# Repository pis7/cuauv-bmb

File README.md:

See full documentation here: https://drive.google.com/file/d/17dhruCo_O_wMr_B44XDcn42W5i2I06rd/view

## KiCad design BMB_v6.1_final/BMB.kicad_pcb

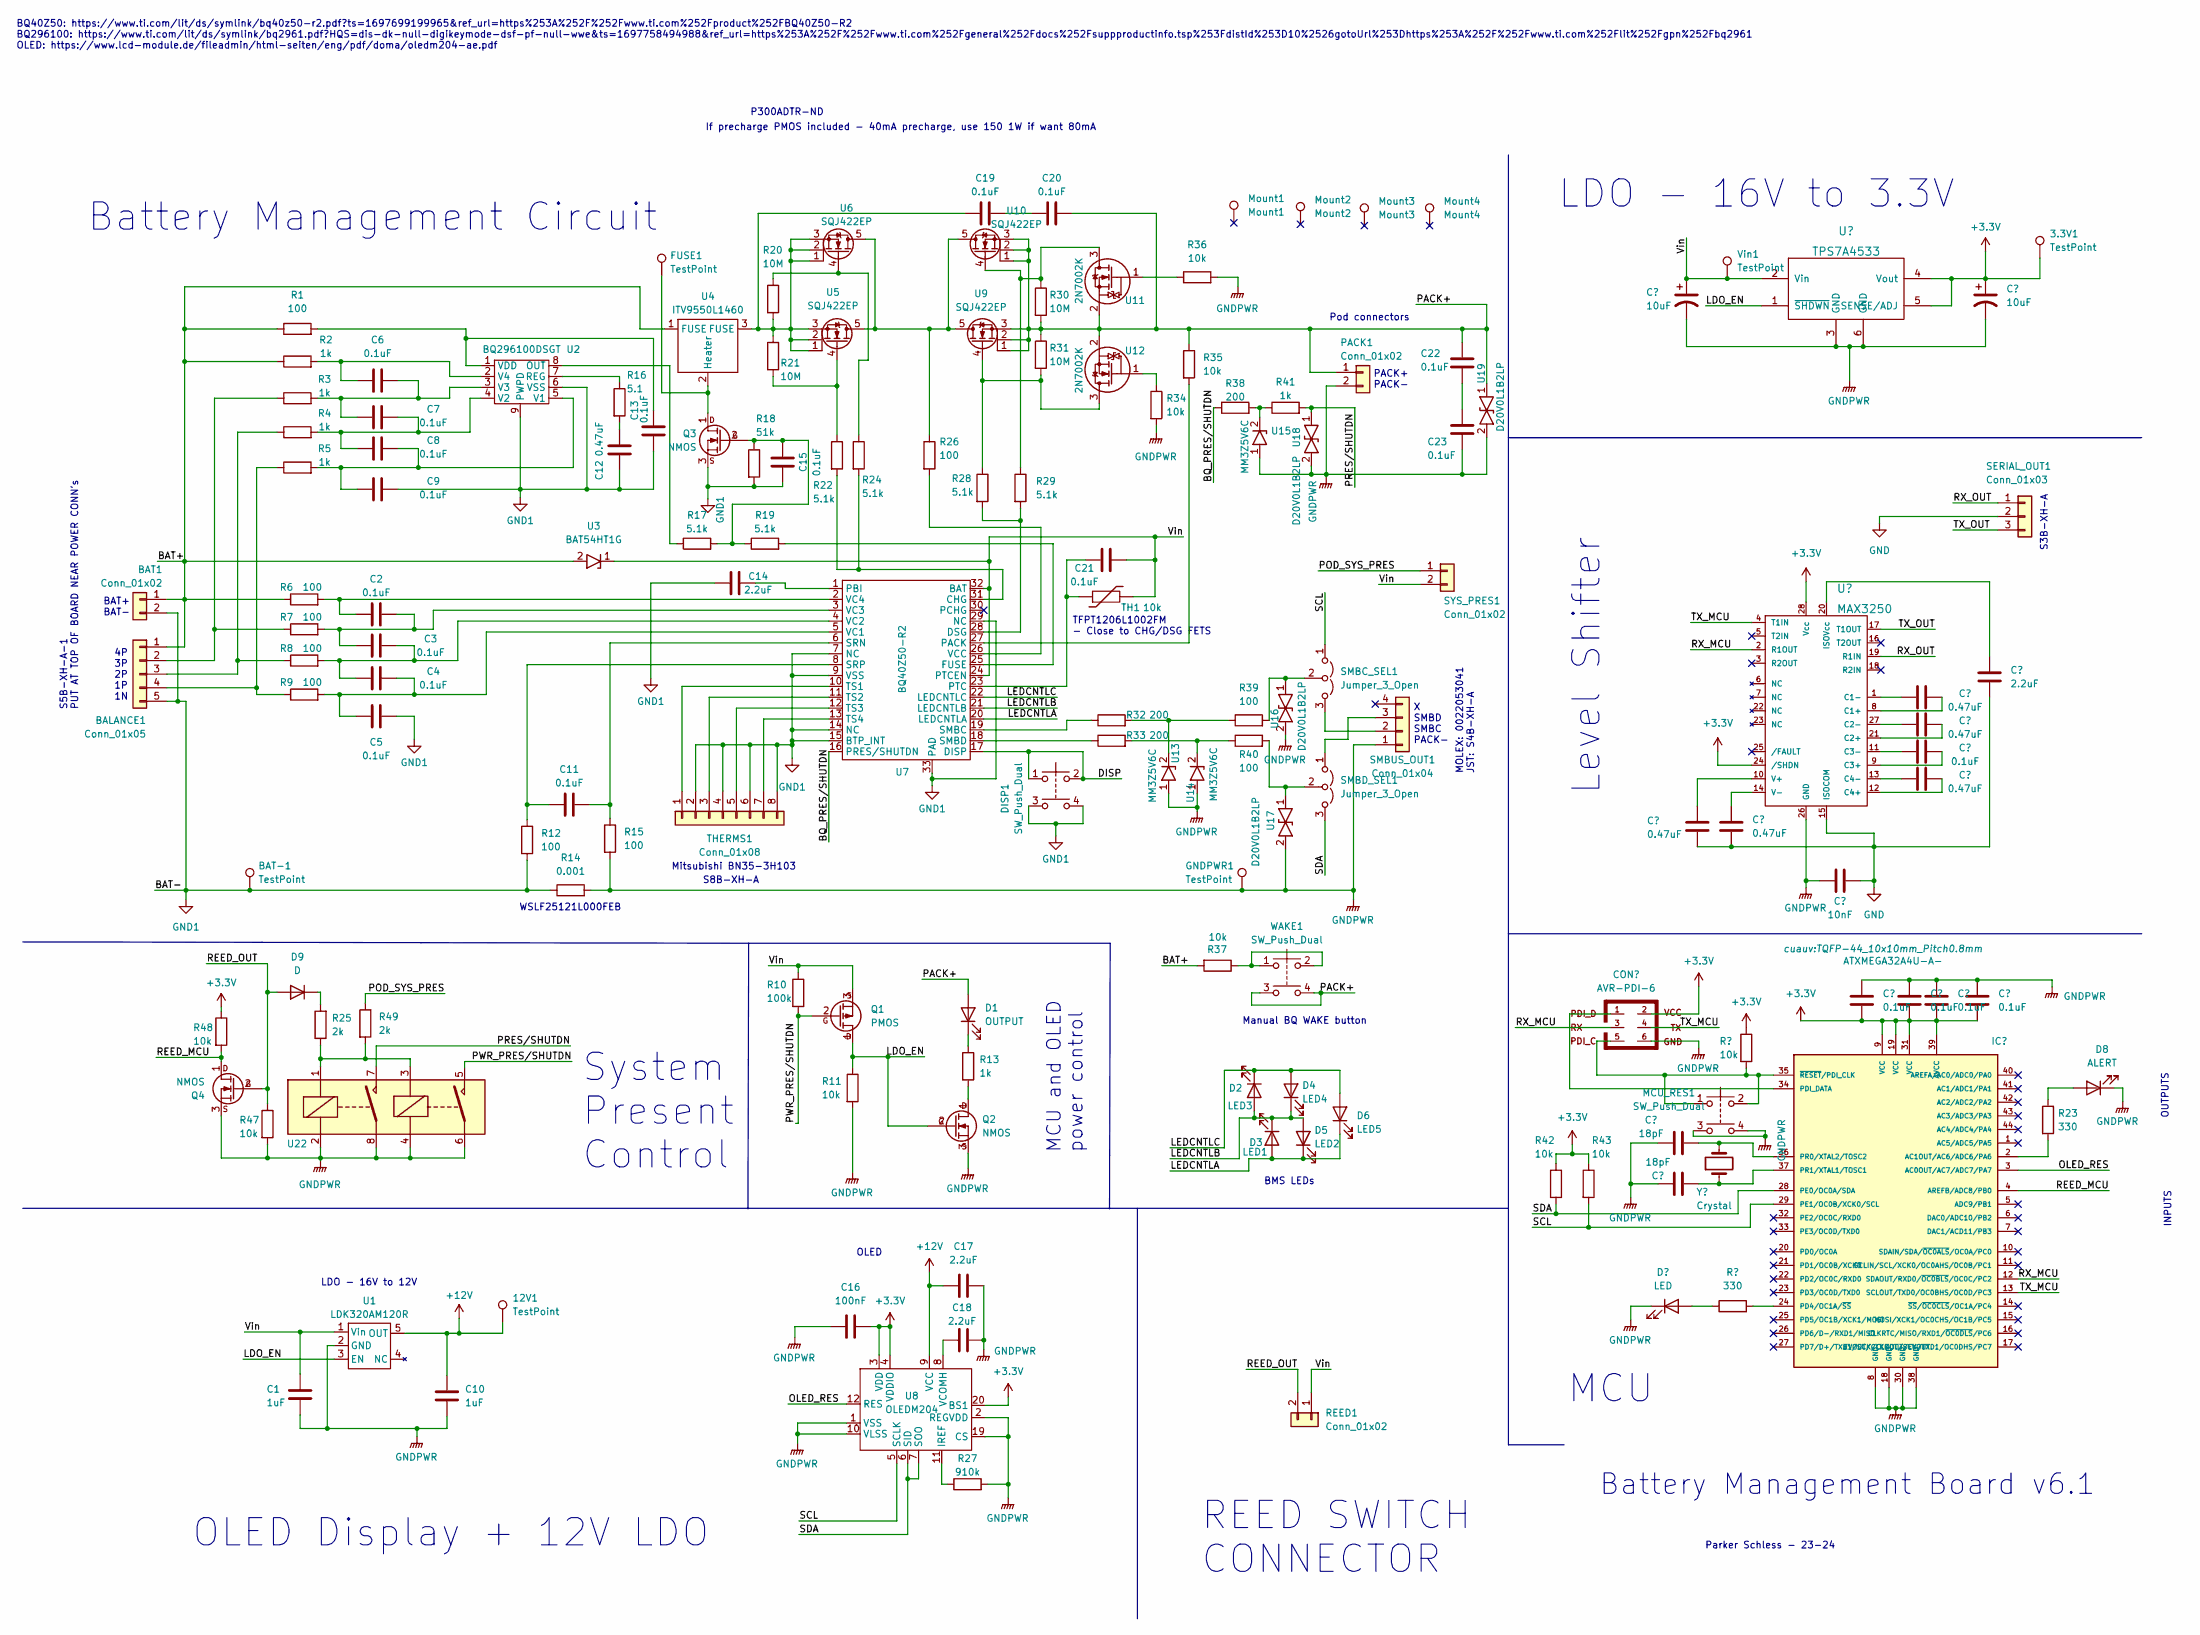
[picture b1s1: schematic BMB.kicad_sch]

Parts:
3.3V1, 12V1: TestPoint; TESTPOINT
BALANCE1: Conn_01x05; CONN_S5B-XH-A-1LFSN_JST
BAT1: Conn_01x02; WetNoodle
BAT-1: TestPoint; TESTPOINT
C1, C10: 1uF; C_0805
C2, C3, C4, C5, C6, C7, C8, C9, C11, C13, C15, C19, C20, C21, C22, C23, C30, C31, C34, C36, C37: 0.1uF; C_0805
C12, C27, C28, C32, C33, C35: 0.47uF; C_0805
C14, C17, C18, C39: 2.2uF; C_0805
C16: 100nF; C_0805
C24, C25: 18pF; C_0805
C26, C38: 10uF; C_0805
C29: 10nF; C_0805
D1: OUTPUT; LED_0805
D2: LED3; LED_0805
D3: LED1; LED_0805
D4: LED4; LED_0805
D5: LED2; LED_0805
D6: LED5; LED_0805
D7: LED; LED_0805
D8: ALERT; LED_0805
D9: D; D_SOD-323
DISP1: SW_Push_Dual; PTS810_CNK
FUSE1: TestPoint; TESTPOINT
GNDPWR1: TestPoint; TESTPOINT
IC1: ATXMEGA32A4U-A-; TQFP-44_10x10mm_Pitch0.8mm
MCU_RES1: SW_Push_Dual; PTS810_CNK
Mount1: Mount1; MountingHole_3.2mm_M3_DIN965_Pad
Mount2: Mount2; MountingHole_3.2mm_M3_DIN965_Pad
Mount3: Mount3; MountingHole_3.2mm_M3_DIN965_Pad
Mount4: Mount4; MountingHole_3.2mm_M3_DIN965_Pad
PACK1: Conn_01x02; WetNoodle
PROG1: AVR-PDI-6; PDI_Header
Q1: PMOS; SOT-23-3
Q2, Q3, Q4: NMOS; SOT-23-3
R1, R6, R7, R8, R9, R12, R15, R26, R39, R40: 100; R_0805
R2, R3, R4, R5, R13, R41: 1k; R_0805
R10: 100k; R_0805
R11, R34, R35, R36, R37, R42, R43, R45, R47, R48: 10k; R_0805
R14: 0.001; R_2512
R16: 5.1; R_0805
R17, R19, R22, R24, R28, R29: 5.1k; R_0805
R18: 51k; R_0805
R20, R21, R30, R31: 10M; R_0805
R23, R44: 330; R_0805
R25, R49: 2k; R_0805
R27: 910k; R_0805
R32, R33, R38: 200; R_0805
REED1: Conn_01x02; CONN_S2B-XH-A-1LFSN_JST
SERIAL_OUT1: Conn_01x03; SHDRRA3W64P0X250_1X3_990X1150X610P
SMBC_SEL1: Jumper_3_Open; PinHeader_1x03_P2.54mm_Vertical
SMBD_SEL1: Jumper_3_Open; PinHeader_1x03_P2.54mm_Vertical
SMBUS_OUT1: Conn_01x04; JST_S4B-XH-A-1
SYS_PRES1: Conn_01x02; CONN_S2B-XH-A-1LFSN_JST
TH1: 10k; R_1206
THERMS1: Conn_01x08; JST_S8B-XH-A-1_LF__SN_
U1: LDK320AM120R; SOT-23-5
U2: BQ296100DSGT; WSON-8-1EP_2x2mm_P0.5mm_EP0.9x1.6mm
U3: BAT54HT1G; SOD-323
U4: ITV9550L1460; ITV9550L1460MR
U5, U6, U9, U10: SQJ422EP
U7: BQ40Z50-R2; QFN-32-1EP_4x4mm_P0.4mm_EP2.65x2.65mm
U8: OLEDM204
U11, U12: 2N7002K; SOT-23
U13, U14, U15: MM3Z5V6C; SOD-323
U16, U17, U18, U19: D20V0L1B2LP; X1-DFN1006-2
U20: MAX3250; SSOP-28_5.3x10.2mm_Pitch0.65mm
U21: TPS7A4533; SOT-223-6_TabPin3
U22: G3VM-62J1(TR)
Vin1: TestPoint; TESTPOINT
WAKE1: SW_Push_Dual; PTS810_CNK
Y1: Crystal; Crystal_Common

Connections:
+3.3V: 3.3V1.1, C16.2, C30.2, C31.2, C36.2, C37.2, C38.1, IC1.9 (VCC), IC1.19 (VCC), IC1.31 (VCC), IC1.39 (AVCC), PROG1.2, R42.1, R43.1, R45.1, R48.1, U8.3 (VDD), U8.4 (VDDIO), U8.20 (BS1), U20.24 (/SHDN), U20.28 (Vcc), U21.4 (Vout), U21.5 (SENSE/ADJ)
+12V: 12V1.1, C10.1, C17.1, U1.5 (OUT), U8.9 (VCC)
/BAT+: BALANCE1.1, BAT1.1, R1.1, R2.1, R6.1, R37.2, U3.2, U4.1 (FUSE)
/BQ_PRES/SHUTDN: R38.1, U7.16 (PRES/SHUTDN)
/DISP: DISP1.1, DISP1.2, U7.17 (DISP)
/LDO_EN: Q1.1 (D), Q2.2 (G), R11.1, U1.3 (EN), U21.1 (~SHDWN)
/LEDCNTLA: D3.2 (A), D5.1 (K), D6.1 (K), U7.20 (LEDCNTLA)
/LEDCNTLB: D2.2 (A), D3.1 (K), D4.1 (K), D5.2 (A), U7.21 (LEDCNTLB)
/LEDCNTLC: D2.1 (K), D4.2 (A), D6.2 (A), U7.22 (LEDCNTLC)
/OLED_RES: IC1.3 (AC0OUT/AC7/ADC7/PA7), U8.12 (RES)
/PACK+: C20.2, C22.1, D1.2 (A), PACK1.1, R30.2, R31.1, R35.1, U9.1, U9.2, U9.3, U10.1, U10.2, U10.3, U11.2, U12.2, U19.1, WAKE1.3, WAKE1.4
/POD_SYS_PRES: R49.1, SYS_PRES1.1
/PRES/SHUTDN: R41.2, U18.1, U22.7
/PWR_PRES/SHUTDN: Q1.2 (G), R10.2, U22.5
/REED_MCU: IC1.4 (AREFB/ADC8/PB0), Q4.1 (D), R48.2
/REED_OUT: D9.2 (A), Q4.2 (G), R47.1, REED1.2
/RX_MCU: IC1.12 (SDAOUT/RXD0/~OC0BLS/OC0C/PC2), PROG1.3, U20.2 (R1OUT)
/RX_OUT: SERIAL_OUT1.1, U20.19 (R1IN)
/SCL: IC1.29 (PE1/OC0B/XCK0/SCL), R43.2, SMBC_SEL1.1 (A), U8.5 (SCLK)
/SDA: IC1.28 (PE0/OC0A/SDA), R42.2, SMBD_SEL1.3 (B), U8.6 (SID), U8.7 (SOO)
/TX_MCU: IC1.13 (SCLOUT/TXD0/OC0BHS/OC0D/PC3), PROG1.4, U20.4 (T1IN)
/TX_OUT: SERIAL_OUT1.3, U20.17 (T1OUT)
/Vin: C1.1, C21.2, C26.1, Q1.3 (S), R10.1, REED1.1, SYS_PRES1.2, TH1.2, U1.1 (Vin), U3.1, U7.24 (PTCEN), U7.32 (BAT), U21.2 (Vin), Vin1.1
GND: C27.2, C28.2, C29.2, C39.2, SERIAL_OUT1.2, U20.15 (ISOCOM)
GND1: BALANCE1.5, BAT1.2, BAT-1.1, C5.2, C9.2, C12.1, C13.1, C14.1, C15.1, DISP1.3, DISP1.4, Q3.3 (S), R12.2, R14.1, R18.2, THERMS1.2, THERMS1.4, THERMS1.6, THERMS1.8, U2.6 (VSS), U2.9 (PWPD), U7.7 (NC), U7.9 (VSS), U7.14 (NC), U7.15 (BTP_INT), U7.29 (NC), U7.33 (PAD)
GNDPWR: C1.2, C10.2, C16.1, C17.2, C18.2, C23.2, C24.1, C25.1, C26.2, C29.1, C30.1, C31.1, C36.1, C37.1, C38.2, D7.1 (K), D8.1 (K), GNDPWR1.1, IC1.8 (GND), IC1.18 (GND), IC1.30 (GND), IC1.38 (GND), MCU_RES1.3, MCU_RES1.4, PACK1.2, PROG1.6, Q2.3 (S), Q4.3 (S), R11.2, R14.2, R15.2, R27.2, R34.2, R36.2, R47.2, SMBUS_OUT1.1, U1.2 (GND), U8.1 (VSS), U8.2 (REGVDD), U8.10 (VLSS), U8.19 (CS), U13.1, U14.1, U15.1, U16.2, U17.2, U18.2, U19.2, U20.26 (GND), U21.3 (GND), U21.6 (GND), U22.2, U22.4, U22.6, U22.8
unnamed: BALANCE1.2, R3.1, R7.1
unnamed: BALANCE1.3, R4.1, R8.1
unnamed: BALANCE1.4, R5.1, R9.1
unnamed: C12.2, R16.2
unnamed: C19.1, R20.2, R21.1, U4.3 (FUSE), U5.1, U5.2, U5.3, U6.1, U6.2, U6.3
unnamed: C19.2, C20.1
unnamed: C22.2, C23.1
unnamed: D1.1 (K), R13.1
unnamed: D7.2 (A), R44.1
unnamed: D8.2 (A), R23.1
unnamed: D9.1 (K), R25.2
unnamed: IC1.2 (AC1OUT/AC6/ADC6/PA6), R23.2
unnamed: IC1.24 (PD4/OC1A/~SS), R44.2
unnamed: IC1.34 (PDI_DATA), PROG1.1
unnamed: C24.2, IC1.36 (PR0/XTAL2/TOSC2), Y1.2
unnamed: C25.2, IC1.37 (PR1/XTAL1/TOSC1), Y1.1
unnamed: IC1.35 (~RESET/PDI_CLK), MCU_RES1.1, MCU_RES1.2, PROG1.5, R45.2
unnamed: Q2.1 (D), R13.2
unnamed: FUSE1.1, Q3.1 (D), U4.2 (Heater)
unnamed: C15.2, Q3.2 (G), R17.2, R18.1, R19.1
unnamed: R20.1, R24.1, U6.4
unnamed: R21.2, R22.1, U5.4
unnamed: R25.1, R49.2, U22.1, U22.3
unnamed: R26.1, U5.5, U6.5, U9.5, U10.5
unnamed: R28.1, R31.2, U9.4, U12.3
unnamed: R29.1, R30.1, U10.4, U11.3
unnamed: R32.2, R39.1, U13.2
unnamed: R33.2, R40.1, U14.2
unnamed: R34.1, U12.1
unnamed: R36.1, U11.1
unnamed: R37.1, WAKE1.1, WAKE1.2
unnamed: R38.2, R41.1, U15.2
unnamed: SMBC_SEL1.3 (B), SMBUS_OUT1.2
unnamed: R39.2, SMBC_SEL1.2 (C), U16.1
unnamed: SMBD_SEL1.1 (A), SMBUS_OUT1.3
unnamed: R40.2, SMBD_SEL1.2 (C), U17.1
unnamed: THERMS1.1, U7.10 (TS1)
unnamed: THERMS1.3, U7.11 (TS2)
unnamed: THERMS1.5, U7.12 (TS3)
unnamed: THERMS1.7, U7.13 (TS4)
unnamed: R17.1, U2.8 (OUT)
unnamed: R16.1, U2.7 (REG)
unnamed: C8.2, C9.1, R5.2, U2.5 (V1)
unnamed: C7.2, C8.1, R4.2, U2.4 (V2)
unnamed: C6.2, C7.1, R3.2, U2.3 (V3)
unnamed: C6.1, R2.2, U2.2 (V4)
unnamed: C13.2, R1.2, U2.1 (VDD)
unnamed: R22.2, R24.2, U7.31 (CHG)
unnamed: R28.2, R29.2, U7.28 (DSG)
unnamed: R19.2, U7.25 (FUSE)
unnamed: R35.2, U7.27 (PACK)
unnamed: C14.2, U7.1 (PBI)
unnamed: C21.1, TH1.1, U7.23 (PTC)
unnamed: R32.1, U7.19 (SMBC)
unnamed: R33.1, U7.18 (SMBD)
unnamed: C11.2, R15.1, U7.6 (SRN)
unnamed: C11.1, R12.1, U7.8 (SRP)
unnamed: C4.2, C5.1, R9.2, U7.5 (VC1)
unnamed: C3.2, C4.1, R8.2, U7.4 (VC2)
unnamed: C2.2, C3.1, R7.2, U7.3 (VC3)
unnamed: C2.1, R6.2, U7.2 (VC4)
unnamed: R26.2, U7.26 (VCC)
unnamed: R27.1, U8.11 (IREF)
unnamed: C18.1, U8.8 (VCOMH)
unnamed: C32.2, U20.8 (C1+)
unnamed: C32.1, U20.1 (C1-)
unnamed: C33.2, U20.21 (C2+)
unnamed: C33.1, U20.27 (C2-)
unnamed: C34.2, U20.9 (C3+)
unnamed: C34.1, U20.11 (C3-)
unnamed: C35.2, U20.12 (C4+)
unnamed: C35.1, U20.13 (C4-)
unnamed: C39.1, U20.20 (ISOVcc)
unnamed: C27.1, U20.10 (V+)
unnamed: C28.1, U20.14 (V-)

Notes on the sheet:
WSLF25121L000FEB
REED SWITCH CONNECTOR
X SMBD SMBC PACK-
PACK+ PACK-
Manual BQ WAKE button
MCU
BQ40Z50: https://www.ti.com/lit/ds/symlink/bq40z50-r2.pdf?ts=1697699199965&ref_url=https%253A%252F%252Fwww.ti.com%252Fproduct%252FBQ40Z50-R2 BQ296100: https://www.ti.com/lit/ds/symlink/bq2961.pdf?HQS=dis-dk-null-digikeymode-dsf-pf-null-wwe&ts=1697758494988&ref_url=https%253A%252F%252Fwww.ti.com%252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
Battery Management Board v6.1
S8B-XH-A
LDO - 16V to 12V
S3B-XH-A
TFPT1206L1002FM - Close to CHG/DSG FETS
Level Shifter
If precharge PMOS included - 40mA precharge, use 150 1W if want 80mA
OLED Display + 12V LDO
BMS LEDs
MCU and OLED power control
OUTPUTS
Battery Management Circuit
OLED
LDO - 16V to 3.3V
MOLEX: 0022053041 JST: S4B-XH-A
Mitsubishi BN35-3H103
S5B-XH-A-1 PUT AT TOP OF BOARD NEAR POWER CONN's
BAT+ BAT-
Pod connectors
INPUTS
System Present Control
4P 3P 2P 1P 1N
Parker Schless - 23-24
P300ADTR-ND

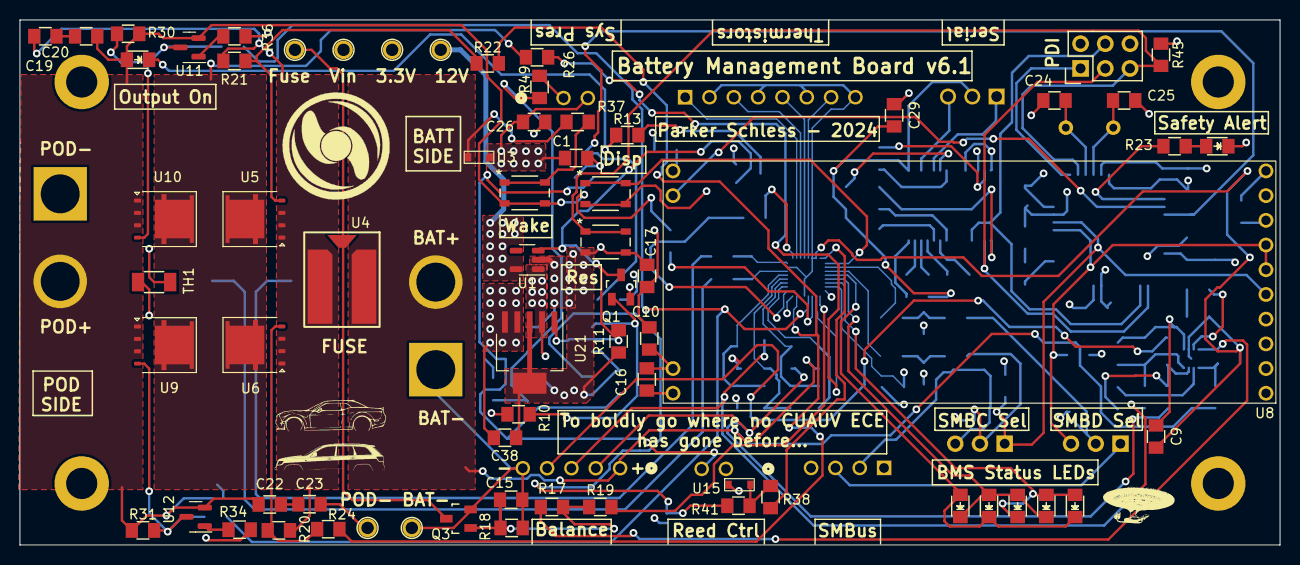
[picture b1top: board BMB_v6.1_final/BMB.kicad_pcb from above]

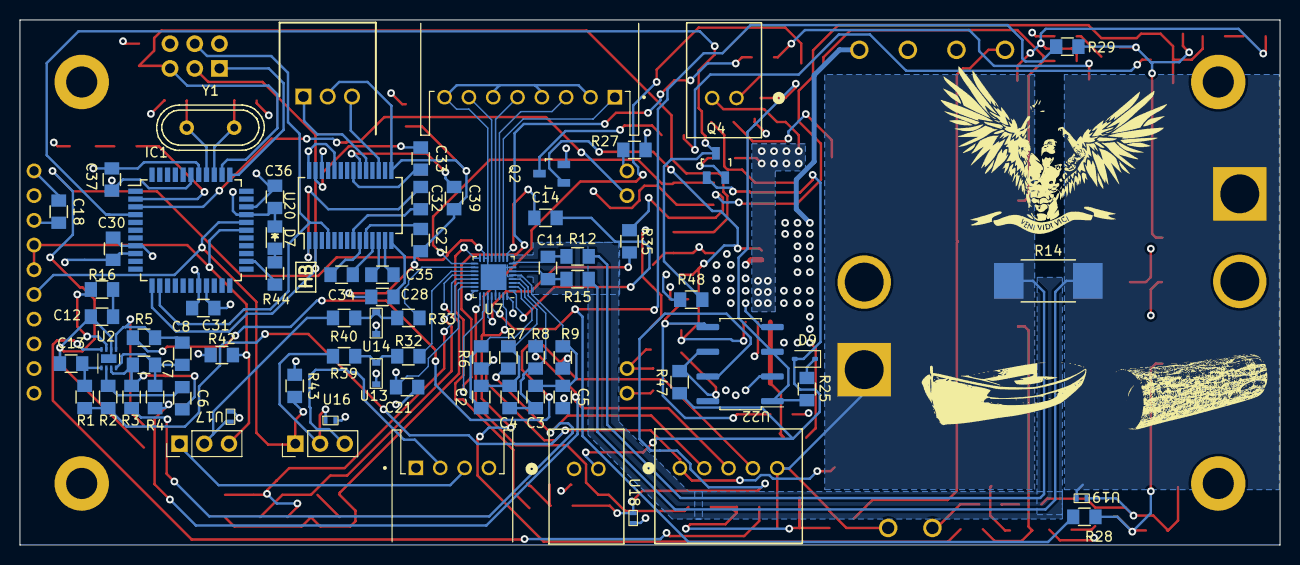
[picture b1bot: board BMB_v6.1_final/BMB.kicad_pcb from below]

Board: 4 copper layers, 129.5 x 54.0 mm, 154 parts (77 on the bottom side), 101 nets.

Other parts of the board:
G1: LOGO; cuauv_prop
G3: LOGO; chally
G4: LOGO; boat_fp
G5: LOGO; log_fp
G6: LOGO; wk2

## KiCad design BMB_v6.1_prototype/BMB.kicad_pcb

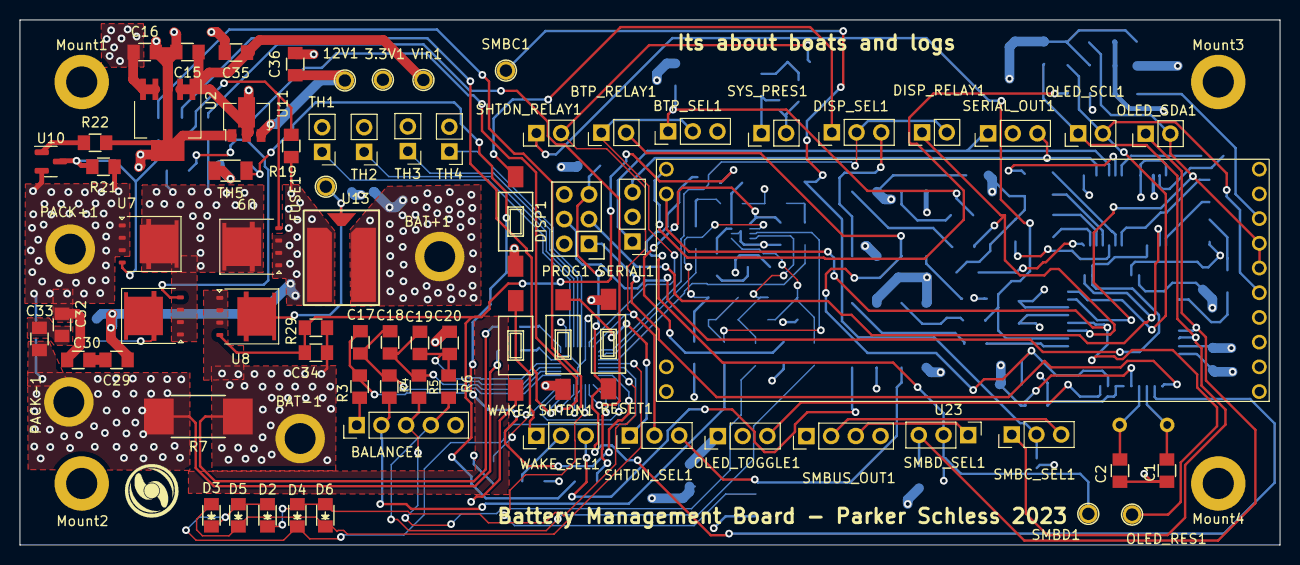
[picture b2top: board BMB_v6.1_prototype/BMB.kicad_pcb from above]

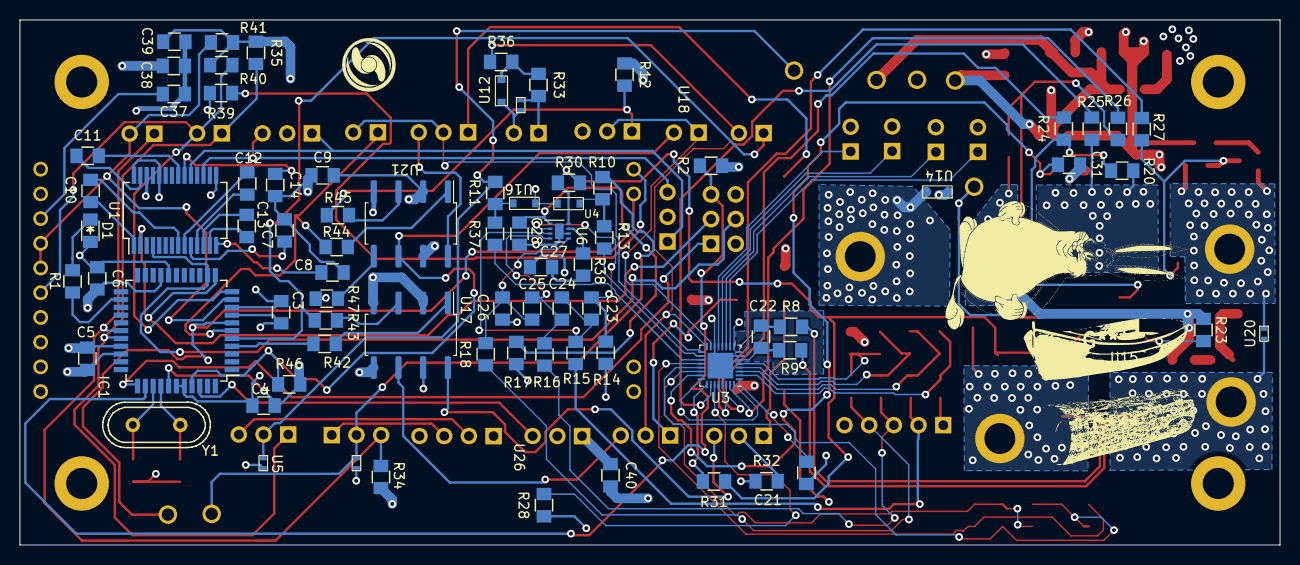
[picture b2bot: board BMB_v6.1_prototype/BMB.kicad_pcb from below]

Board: 4 copper layers, 129.5 x 54.0 mm, 159 parts (79 on the bottom side), 110 nets.

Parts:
3.3V1: 3.3V; TESTPOINT
12V1: 12V; TESTPOINT
BALANCE1: Conn_01x05; PinHeader_1x05_P2.54mm_Vertical
BAT+1: Conn_01x01; WetNoodle_Singular
BAT-1: Conn_01x01; WetNoodle_Singular
BTP_RELAY1: Jumper_2_Open; PinHeader_1x02_P2.54mm_Vertical
BTP_SEL1: Jumper_3_Open; PinHeader_1x03_P2.54mm_Vertical
C1, C2: 18pF; C_0805
C3, C4, C5, C6, C12, C17, C18, C19, C20, C22, C23, C24, C25, C26, C28, C29, C30, C31, C32, C33, C34, C40: 0.1uF; C_0805
C7, C8, C10, C11, C13, C27: 0.47uF; C_0805
C9: 10nF; C_0805
C14, C21, C37, C38: 2.2uF; C_0805
C15, C16: 10uF; C_0805
C35, C36: 1uF; C_0805
C39: 100nF; C_0805
D1: LED; LED_0805
D2: LED3; LED_0805
D3: LED1; LED_0805
D4: LED4; LED_0805
D5: LED2; LED_0805
D6: LED5; LED_0805
DISP1: SW_Push; BUTTON
DISP_RELAY1: Jumper_2_Open; PinHeader_1x02_P2.54mm_Vertical
DISP_SEL1: Jumper_3_Open; PinHeader_1x03_P2.54mm_Vertical
FUSE1: FUSE; TESTPOINT
IC1: ATXMEGA32A4U-A-; TQFP-44_10x10mm_Pitch0.8mm
Mount1: Mount1; MountingHole_3.2mm_M3_DIN965_Pad
Mount2: Mount2; MountingHole_3.2mm_M3_DIN965_Pad
Mount3: Mount3; MountingHole_3.2mm_M3_DIN965_Pad
Mount4: Mount4; MountingHole_3.2mm_M3_DIN965_Pad
OLED_RES1: OLED_RES; TESTPOINT
OLED_SCL1: Jumper_2_Open; PinHeader_1x02_P2.54mm_Vertical
OLED_SDA1: Jumper_2_Open; PinHeader_1x02_P2.54mm_Vertical
OLED_TOGGLE1: Conn_01x03; PinHeader_1x03_P2.54mm_Vertical
PACK+1: Conn_01x01; WetNoodle_Singular
PACK-1: Conn_01x01; WetNoodle_Singular
PROG1: AVR-PDI-6; PDI_Header
R1: 330; R_0805
R2, R22, R28, R32, R40, R41, R46: 10k; R_0805
R3, R4, R5, R6, R8, R9, R10, R11, R17, R25: 100; R_0805
R7: 0.001; R_2512
R12, R34, R35, R47: DNP; R_0805
R13, R36, R37: 200; R_0805
R14, R15, R16, R18, R33: 1k; R_0805
R19, R20, R21: 10M; R_0805
R23: 300; R_0805
R24, R26, R27, R30, R31: 5.1k; R_0805
R29: 51k; R_0805
R38: 5.1; R_0805
R39: 910k; R_0805
R42, R43, R44, R45: 215; R_0805
RESET1: SW_Push; BUTTON
SERIAL1: Serial_Header; PinHeader_1x03_P2.54mm_Vertical
SERIAL_OUT1: Conn_01x03; PinHeader_1x03_P2.54mm_Vertical
SHTDN1: SW_Push; BUTTON
SHTDN_RELAY1: Jumper_2_Open; PinHeader_1x02_P2.54mm_Vertical
SHTDN_SEL1: Jumper_3_Open; PinHeader_1x03_P2.54mm_Vertical
SMBC1: SMBC; TESTPOINT
SMBC_SEL1: Jumper_3_Open; PinHeader_1x03_P2.54mm_Vertical
SMBD1: SMBD; TESTPOINT
SMBD_SEL1: Jumper_3_Open; PinHeader_1x03_P2.54mm_Vertical
SMBUS_OUT1: Conn_01x04; PinHeader_1x04_P2.54mm_Vertical
SYS_PRES1: Conn_01x02; PinHeader_1x02_P2.54mm_Vertical
TH1, TH2, TH3, TH4: 10k; PinHeader_1x02_P2.54mm_Vertical
TH5: 10k; R_1206
U1: MAX3250; SSOP-28_5.3x10.2mm_Pitch0.65mm
U2: TPS7A4533; SOT-223-6_TabPin3
U3: BQ40Z50-R2; QFN-32-1EP_4x4mm_P0.4mm_EP2.65x2.65mm
U4, U12, U16: MM3Z5V6C; SOD-323
U5, U18, U20, U26: D20V0L1B2LP; X1-DFN1006-2
U6: BQ296100DSGT; WSON-8-1EP_2x2mm_P0.5mm_EP0.9x1.6mm
U7, U8, U9: SQJ422EP
U10: 2N7002K; SOT-23
U11: LDK320ADU120R; SOT-89-3
U13: ITV9550L1460; ITV9550L1460MR
U14: BAT54HT1G; SOD-323
U15: SQJ433EP
U17, U21: G3VM-62J1(TR)
U23: OLEDM204
Vin1: Vin; TESTPOINT
WAKE1: SW_Push; BUTTON
WAKE_SEL1: Jumper_3_Open; PinHeader_1x03_P2.54mm_Vertical
Y1: Crystal; Crystal_Common

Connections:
+3.3V: 3.3V1.1, C3.2, C4.2, C5.2, C6.2, C16.1, C39.2, C40.1, IC1.9 (VCC), IC1.19 (VCC), IC1.31 (VCC), IC1.39 (AVCC), IC1.40 (AREFA/AC0/ADC0/PA0), OLED_TOGGLE1.1, PROG1.2, R2.1, R12.1, R34.1, R35.1, R40.1, R41.1, R47.1, U1.24 (/SHDN), U1.28 (Vcc), U2.4 (Vout), U2.5 (SENSE/ADJ), U23.3 (VDD), U23.4 (VDDIO), U23.20 (BS1)
+12V: 12V1.1, C36.1, C38.1, U11.3 (Vout), U23.9 (VCC)
/BAT+: BALANCE1.1, BAT+1.1, R3.1, R14.1, R17.1, R32.1, U13.1 (FUSE), U14.2
/BTP_INT: BTP_RELAY1.1 (A), BTP_SEL1.2 (C), U3.15 (BTP_INT)
/DISP: DISP_RELAY1.2 (B), DISP_SEL1.2 (C), U3.17 (DISP)
/HALL_OUT: IC1.42 (AC2/ADC2/PA2), OLED_TOGGLE1.3
/LEDCNTLA: D3.2 (A), D5.1 (K), D6.1 (K), U3.20 (LEDCNTLA)
/LEDCNTLB: D2.2 (A), D3.1 (K), D4.1 (K), D5.2 (A), U3.21 (LEDCNTLB)
/LEDCNTLC: D2.1 (K), D4.2 (A), D6.2 (A), U3.22 (LEDCNTLC)
/MCU_BTP_INT: BTP_RELAY1.2 (B), IC1.41 (AC1/ADC1/PA1), R46.1, U21.6
/MCU_DISP: DISP_RELAY1.1 (A), IC1.6 (DAC0/ADC10/PB2), R44.1
/MCU_SHUTDN: IC1.5 (ADC9/PB1), R43.1, SHTDN_RELAY1.1 (A)
/MCU_WAKE: IC1.4 (AREFB/ADC8/PB0), R42.1
/OLED_RES: IC1.7 (DAC1/ACD11/PB3), OLED_RES1.1, U23.12 (RES)
/OLED_SCL: IC1.11 (SCLIN/SCL/XCK0/OC0AHS/OC0B/PC1), OLED_SCL1.2 (B), R40.2, U23.5 (SCLK)
/OLED_SDA: IC1.10 (SDAIN/SDA/~OC0ALS/OC0A/PC0), OLED_SDA1.2 (B), R41.2, U23.6 (SID), U23.7 (SOO)
/PACK+: C30.2, C32.1, PACK+1.1, R21.1, R28.1, U7.1, U7.2, U7.3, U10.2, U17.7, U20.1, WAKE1.2
/PRES/SHUTDN: R36.1, SHTDN_RELAY1.2 (B), SHTDN_SEL1.2 (C), U3.16 (PRES/SHUTDN)
/RX_MCU: IC1.12 (SDAOUT/RXD0/~OC0BLS/OC0C/PC2), PROG1.3, U1.2 (R1OUT)
/RX_OUT: SERIAL1.1 (RX), SERIAL_OUT1.1, U1.19 (R1IN)
/SMBC_MCU: IC1.29 (PE1/OC0B/XCK0/SCL), OLED_SCL1.1 (A), R35.2, SMBC_SEL1.1 (A)
/SMBD_MCU: IC1.28 (PE0/OC0A/SDA), OLED_SDA1.1 (A), R34.2, SMBD_SEL1.3 (B)
/TX_MCU: IC1.13 (SCLOUT/TXD0/OC0BHS/OC0D/PC3), PROG1.4, U1.4 (T1IN)
/TX_OUT: SERIAL1.3 (TX), SERIAL_OUT1.3, U1.17 (T1OUT)
/Vin: C15.1, C31.2, C35.1, TH5.2, U2.1 (~SHDWN), U2.2 (Vin), U3.24 (PTCEN), U3.32 (BAT), U11.2 (Vin), U14.1, Vin1.1
GND: C7.2, C8.2, C9.2, C14.2, SERIAL1.2 (GND), SERIAL_OUT1.2, U1.15 (ISOCOM)
GND1: BALANCE1.5, BAT-1.1, BTP_SEL1.3 (B), C20.2, C21.1, C26.2, C27.1, C28.1, C34.1, DISP1.2, R7.1, R8.2, R29.2, SHTDN1.2, TH1.2, TH2.2, TH3.2, TH4.2, U3.7 (NC), U3.9 (VSS), U3.14 (NC), U3.29 (NC), U3.33 (PAD), U6.6 (VSS), U6.9 (PWPD), U8.1, U8.2, U8.3, U17.5, U21.4, U21.7
GNDPWR: C1.1, C2.1, C3.1, C4.1, C5.1, C6.1, C9.1, C15.2, C16.2, C33.2, C35.2, C36.2, C37.2, C38.2, C39.1, C40.2, D1.2 (A), IC1.8 (GND), IC1.18 (GND), IC1.30 (GND), IC1.38 (GND), OLED_TOGGLE1.2, PACK-1.1, PROG1.6, R7.2, R9.2, R22.2, R39.2, R46.2, RESET1.2, SMBUS_OUT1.1, SYS_PRES1.2, U1.26 (GND), U2.3 (GND), U2.6 (GND), U4.1, U5.2, U11.1 (GND), U12.1, U16.1, U17.2, U17.4, U18.2, U20.2, U21.2, U23.1 (VSS), U23.2 (REGVDD), U23.10 (VLSS), U23.19 (CS), U26.2
unnamed: BALANCE1.2, R4.1, R15.1
unnamed: BALANCE1.3, R5.1, R16.1
unnamed: BALANCE1.4, R6.1, R18.1
unnamed: BTP_SEL1.1 (A), R12.2, R45.2
unnamed: C27.2, R38.2
unnamed: C29.1, R19.1, R23.1, U9.1, U9.2, U9.3, U13.3 (FUSE)
unnamed: C29.2, C30.1
unnamed: C32.2, C33.1
unnamed: C34.2, R29.1, R30.2, R31.1, U8.4
unnamed: D1.1 (K), R1.1
unnamed: DISP1.1, DISP_SEL1.1 (A)
unnamed: DISP_SEL1.3 (B), U21.8
unnamed: IC1.24 (PD4/OC1A/~SS), R1.2
unnamed: IC1.34 (PDI_DATA), PROG1.1
unnamed: C1.2, IC1.36 (PR0/XTAL2/TOSC2), Y1.2
unnamed: C2.2, IC1.37 (PR1/XTAL1/TOSC1), Y1.1
unnamed: IC1.35 (~RESET/PDI_CLK), PROG1.5, R2.2, RESET1.1
unnamed: R10.1, R13.2, U4.2
unnamed: R11.1, R37.2, U16.2
unnamed: R19.2, R26.1, U9.4
unnamed: R20.1, R24.1, U15.4
unnamed: R20.2, R25.1, U7.5, U9.5, U15.1, U15.2, U15.3
unnamed: R21.2, R27.1, U7.4, U10.3
unnamed: R22.1, U10.1
unnamed: R23.2, U15.5
unnamed: R33.1, R36.2, U12.2
unnamed: R42.2, U17.1
unnamed: R43.2, U17.3
unnamed: R44.2, U21.1
unnamed: R45.1, U21.3
unnamed: R47.2, U21.5
unnamed: SHTDN1.1, SHTDN_SEL1.1 (A)
unnamed: SHTDN_SEL1.3 (B), U17.6
unnamed: SMBC_SEL1.3 (B), SMBUS_OUT1.2
unnamed: R11.2, SMBC1.1, SMBC_SEL1.2 (C), U5.1
unnamed: SMBD_SEL1.1 (A), SMBUS_OUT1.3
unnamed: R10.2, SMBD1.1, SMBD_SEL1.2 (C), U26.1
unnamed: R33.2, SYS_PRES1.1, U18.1
unnamed: C10.2, U1.8 (C1+)
unnamed: C10.1, U1.1 (C1-)
unnamed: C11.2, U1.21 (C2+)
unnamed: C11.1, U1.27 (C2-)
unnamed: C12.2, U1.9 (C3+)
unnamed: C12.1, U1.11 (C3-)
unnamed: C13.2, U1.12 (C4+)
unnamed: C13.1, U1.13 (C4-)
unnamed: C14.1, U1.20 (ISOVcc)
unnamed: C7.1, U1.10 (V+)
unnamed: C8.1, U1.14 (V-)
unnamed: R26.2, U3.31 (CHG)
unnamed: R27.2, U3.28 (DSG)
unnamed: R31.2, U3.25 (FUSE)
unnamed: R28.2, U3.27 (PACK)
unnamed: C21.2, U3.1 (PBI)
unnamed: R24.2, U3.30 (PCHG)
unnamed: C31.1, TH5.1, U3.23 (PTC)
unnamed: R37.1, U3.19 (SMBC)
unnamed: R13.1, U3.18 (SMBD)
unnamed: C22.2, R9.1, U3.6 (SRN)
unnamed: C22.1, R8.1, U3.8 (SRP)
unnamed: TH1.1, U3.10 (TS1)
unnamed: TH2.1, U3.11 (TS2)
unnamed: TH3.1, U3.12 (TS3)
unnamed: TH4.1, U3.13 (TS4)
unnamed: C19.2, C20.1, R6.2, U3.5 (VC1)
unnamed: C18.2, C19.1, R5.2, U3.4 (VC2)
unnamed: C17.2, C18.1, R4.2, U3.3 (VC3)
unnamed: C17.1, R3.2, U3.2 (VC4)
unnamed: R25.2, U3.26 (VCC)
unnamed: R30.1, U6.8 (OUT)
unnamed: R38.1, U6.7 (REG)
unnamed: C25.2, C26.1, R18.2, U6.5 (V1)
unnamed: C24.2, C25.1, R16.2, U6.4 (V2)
unnamed: C23.2, C24.1, R15.2, U6.3 (V3)
unnamed: C23.1, R14.2, U6.2 (V4)
unnamed: C28.2, R17.2, U6.1 (VDD)
unnamed: FUSE1.1, U8.5, U13.2 (Heater)
unnamed: R39.1, U23.11 (IREF)
unnamed: C37.1, U23.8 (VCOMH)
unnamed: WAKE1.1, WAKE_SEL1.1 (A)
unnamed: U17.8, WAKE_SEL1.3 (B)
unnamed: R32.2, WAKE_SEL1.2 (C)

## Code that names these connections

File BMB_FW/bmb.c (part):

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
void gpio_init()
{
	// PA0 = REED_MCU (input)
	PORTB.DIRCLR = PIN0_bm;

	// PA6 = Safety Status LED (output)
	// PA7 = OLED_RES (output)
	PORTA.DIRSET = PIN6_bm | PIN7_bm;
}

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	TCC0.CTRLB = TC_WGMODE_NORMAL_gc;		// Normal operation
	TCC0.INTCTRLA = TC_OVFINTLVL_HI_gc; // Disable error interrupt, enable overflow interrtup (LOW)
	TCC0.PER = 500;											// 500 ticks per interrupt (32MHz/64/500 = 1kHz)
	PORTD.DIRSET |= PIN4_bm;						// set PD4 to be an output (LED Heartbeat pin)
	PMIC.CTRL |= PMIC_HILVLEN_bm;				// enable high level interrupts
}

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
